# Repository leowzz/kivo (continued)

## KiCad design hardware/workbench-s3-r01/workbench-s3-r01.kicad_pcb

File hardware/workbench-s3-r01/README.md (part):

# Workbench S3 r01 - Stacked Breakaway Boards

Independent **routed prototype**, using the YD ESP32-S3 core board from
`refer/YD-ESP32-S3/`. Open `workbench-s3-r01.kicad_pro` in KiCad 10.
The RP2040 design remains in `../workbench-r03/`. Physical module fit and
the fabricator's panel process still require confirmation; this is not a
released product definition. Firmware support remains pending.

## Architecture

- Manufacture a single mechanically connected 126 x 187 mm panel, then cut
  the perforated tabs into an upper key board and a lower controller board.
- Assemble the 126 x 86 mm lower board horizontally and the 126 x 98 mm upper
  board rear-high at a nominal 30 degrees. The PCB projection fits in 86 mm
  depth, compared with 135 mm for the previous single-board draft.
- J8 on the lower board and J9 on the upper underside connect by one **four-wire
  harness: GND, 3V3, SDA, SCL**. No electrical connection crosses the tabs.
- Preassembled YD ESP32-S3 plugs into two 1x22 female sockets, J1 and J7.
- Reuse the core board's native USB Type-C for HID/data and power.
- 18 MX hot-swap keys use a 3x6 matrix with one 1N4148W diode per key.
- An upper-board MCP23017 scans the matrix and five control inputs; it shares
  the display's I2C bus. The application uses just **two ESP32 GPIOs**, 13/14.
- SH1106/EC11/confirm/back module connects by the J2 harness.
- J4 exposes 22 general-purpose spare GPIOs, GND and 3.3 V.
- J5/J6 provide external BOOT/RESET button connections.
- Carrier parts are through-hole connectors, SOD-123 diodes, 0805 passives
  with extended pads, and one SOIC-28 wide chip with 1.27 mm lead pitch.
- No bare MCU, flash, crystal, regulator or fine-pitch USB connector needs
  soldering on this carrier.

## Schematic Pages

Open `workbench-s3-r01.kicad_sch` as the root schematic. Page 1 (A4) contains
the lower board's core sockets, expansion header, BOOT/RESET and J8 cable
connector. Its `Upper` sheet opens page 2 (A3), containing the upper board's
power entry, MCP23017 with local decoupling/reset/I2C pull-ups, display
connector and directly wired 3x6 key/diode matrix. Both schematic files are
required when copying the project.

The upper sheet uses absolute global labels such as `/UP_GPA5` to preserve
the existing routed PCB net names. They do not connect to the lower board;
the external J8/J9 harness still joins the two independent circuits. The
layout retains all component values, footprints, reference designators and
symbol UUIDs. The PCB's upper-component schematic paths are updated for the
new hierarchy; copper, footprints and board geometry are unchanged.

`layout_workbench_s3_schematic.py` provides the shared page layout used by
the generator. `placement.json` records the two schematic paths so a fresh
placement keeps the correct symbol associations. A before/after exported
netlist can be checked using `verify_workbench_s3_schematic.py`.

## Core Board Sockets

The manufacturer's metric drawing specifies 27.94 mm width, 57.15 mm PCB
length, 63.39 mm including the antenna, 25.40 mm between header rows and
53.34 mm between the first and last holes. Both rows have 22 pins at 2.54 mm
pitch; end holes are approximately 1.91 mm from each PCB end.

Viewed from the carrier's component side with USB at the rear/top:

| Carrier | Core Board Row | Position | Pin 1 |
| --- | --- | --- | --- |
| J1 | Manufacturer P1 | Right | 3V3, nearest antenna/front |
| J7 | Manufacturer P2 | Left | GND, nearest antenna/front |

Both socket rows run from pin 1 towards pin 22 at the USB end. The core board
is rotated 180 degrees from the manufacturer's antenna-up illustration.
Use 2.54 mm female sockets with 1.0 mm PCB drills. The two row centers are
25.40 mm apart; do not substitute a narrower ESP32 board footprint.

The full pin mapping, including deliberately unconnected pins, is in
`placement.json`. GPIO19/20 stay exclusively on the module's USB connection.
GPIO35-37 are not used, allowing modules with octal PSRAM. GPIO43/44 remain
with the serial bridge, GPIO48 with the module RGB LED, and GPIO3/45/46 are
not assigned external loads because of boot-strapping constraints.

Power the assembly through the core board. The carrier uses its 3.3 V and GND.
P1 pin 21 is intentionally unconnected: the reference board's 5V pin is on
the input side of diode D3 unless its IN-OUT jumper is fitted. It must not
be assumed to provide USB-derived 5 V. External GPIO and I2C signals are
3.3 V only, and peripheral loads must fit the module regulator's remaining
current and thermal budget.

## Matrix

| Function | MCP23017 Ports |
| --- | --- |
| Rows R0-R2, selected LOW, inactive HIGH | GPA5, GPA6, GPA7 |
| Columns C0-C5, read with internal pull-ups | GPB0, GPB1, GPB2, GPB3, GPB4, GPB5 |

K1-K6 are the rear key row, K7-K12 the middle, and K13-K18 the front.
For every key: column -> switch -> diode anode A -> diode cathode K -> row.
**The stripe on each diode goes to the row net.** D1 belongs to K1, and so on.
Use 1N4148W in SOD-123, not the smaller SOD-323 version.

U1 is **MCP23017-E/SO**, at I2C address **0x20** (A0/A1/A2 tied to ground).
Its SOIC-28 wide package has accessible 1.27 mm pitch leads and no underside
thermal pad; assemble with a soldering iron, flux and solder wick. Do not
substitute MCP23S17 (SPI), SSOP or QFN for this footprint. R4 holds RESET
high, C3 is U1's local 100 nF decoupler, and C1/C2 decouple the upper supply.

The current Microchip datasheet specifies **GPA7 and GPB7 as output-only**.
GPA7 is a row output here; GPB7 is unused. GPB6 is also unused. GPA0-GPA4
read the display module's five control signals. INTA/INTB are unconnected;
firmware polls the ports so the harness needs no interrupt conductor.

This changes total application use from 16 MCU GPIOs to 2, and the inter-board
cable from 20 conductors to 4. Diodes prevent electrical ghost paths; firmware
must still implement matrix debounce and rollover behavior. Configure unused
ports to defined states and preload all row output latches HIGH before
enabling row outputs, then select one LOW at a time.

## Other Interfaces

All pin orders below use each separated board's front/component-side view,
rear edge at the top. The lower board is rotated 180 degrees in the panel.

| J2 Pin | Signal | Destination |
| --- | --- | --- |
| 1, rightmost square pad | VCC / 3.3 V | - |
| 2 | GND | - |
| 3 | BAK / KEY0 / Back | U1 GPA4 |
| 4 | TRB / TRIM_B / Encoder B | U1 GPA3 |
| 5 | TRA / TRIM_A / Encoder A | U1 GPA2 |
| 6 | PSH / PUSH / Encoder press | U1 GPA1 |
| 7 | SCL / IIC_SCL | ESP32 GPIO14 / U1 SCL |
| 8 | SDA / IIC_SDA | ESP32 GPIO13 / U1 SDA |
| 9, leftmost pad | CON / KEY1 / Confirm | U1 GPA0 |

J2 matches the supplied module interface diagram and front photograph in
`references/display-interface.png`. Looking at the readable display with
the encoder on the right, the top connector reads **CON, SDA, SCL, PSH,
TRA, TRB, BAK, GND, VCC from left to right**. This is pin 9 through pin 1.
VCC is **3.3 V only**. Use a pin-for-pin 9-wire harness and identify the
square pad rather than inferring pin numbers from a rear or mating-face view.
The module-side order is unchanged by this I2C revision; only the five
control signals' carrier-side destinations move from ESP32 GPIOs to U1.

The dimension source is `references/display-dimensions.png`. The module's
64.90 x 35.03 mm bounding rectangle is placed at upper-board `(8,3)` mm,
front-facing with the encoder on the right. `Dwgs.User` shows this assembly
envelope, including the notched board's full rectangular extent; it is not
a cutout in the carrier. The module connector runs horizontally near the
rear edge. Its leftmost pin is 11.38 mm from the module's left edge and
the row is 1.93 mm below its top edge. On the carrier, J2 pin 9 is at
`(19.38,4.93)` and pin 1 is at `(39.70,4.93)` mm.

The 2.54 mm header pitch is the standard pitch assumed for this module;
it is not explicitly dimensioned in the supplied drawing. Pin 1's X value
uses `11.38 + 8 * 2.54 = 31.70` mm. Confirm pitch against the purchased
module before fabrication. Carrier J2 uses 1.0 mm plated drills.

Four additional 3.4 mm NPTH clearance holes follow the module's M3 mounting
centers. The drawing's slight asymmetry is retained:

| Mount | Relative To Module Top-Left | Relative To Upper PCB Top-Left |
| --- | --- | --- |
| H_D1, rear left | (2.87, 2.85) | (10.87, 5.85) |
| H_D2, rear right | (61.90, 2.90) | (69.90, 5.90) |
| H_D3, front left | (2.95, 32.06) | (10.95, 35.06) |
| H_D4, front right | (61.93, 31.88) | (69.93, 34.88) |

These module mounts are separate from the upper PCB's four enclosure mounts.
Set module standoff height and header/harness direction from the actual
assembly; this connector is still a harness interface, not a validated
rigid board-to-board mating stack. Keep underside screw heads within the
3.5 mm nominal parts envelope or recheck the stack clearances.

R1/R2 are fitted **2.2 kohm I2C pull-ups to 3.3 V**. Include the display's
parallel pull-ups when calculating the effective resistance. For example,
2.2k in parallel with 4.7k is about 1.5k. Verify low-level sink current and
rise time with both harnesses attached; target at most 300 ns rise time at
400 kHz. Do not connect a module whose I2C pull-ups go to 5 V.

J4 sits at the lower board's rear-left edge. Its 1x24, 2.54 mm pitch plated holes have
1.0 mm drills. From the left square pad to the right:

| Pins | Signals In Pin Order |
| --- | --- |
| 1-6 | GND, 3V3, GPIO1, GPIO2, GPIO4, GPIO5 |
| 7-12 | GPIO6, GPIO7, GPIO8, GPIO9, GPIO10, GPIO11 |
| 13-18 | GPIO12, GPIO15, GPIO16, GPIO17, GPIO18, GPIO21 |
| 19-24 | GPIO38, GPIO39, GPIO40, GPIO41, GPIO42, GPIO47 |

Pin 1 is at `(10,3)` mm and pin 24 at `(68.42,3)` mm. The two button
headers move right to leave this longer expansion row clear: BOOT pin 1
at `(73,4)` and RESET pin 1 at `(80,4)` mm.

J5/J6 sit next to the core board's USB end. Each has two 2.54 mm pitch,
1.0 mm drilled plated holes for a normally-open momentary button with matching
leads, or short wires to a button. These are not universal four-leg button
footprints.

| Header | Left Square Pad, Pin 1 | Right Pad, Pin 2 |
| --- | --- | --- |
| J5 BOOT | GPIO0 | GND |
| J6 RESET | EN / CHIP_PU | GND |

They parallel the core board buttons. R3 adds a 10 kohm BOOT pull-up; the
module already supplies the EN pull-up and reset capacitors. Hold BOOT,
press/release RESET, then release BOOT to request the ROM download mode.

## Board-to-Board Cable

Use two **JST XH B4B-XH-A, 1x4, 2.50 mm pitch, vertical through-hole
headers** and matching XHP-4 housings/crimp contacts. Buy a precrimped,
pin-for-pin four-conductor harness to avoid soldering cable contacts.
Start with 150 mm including service slack. This is **2.50 mm XH**, not a
2.54 mm pin-header or IDC footprint; the PCB drills are 0.95 mm. Match the
actual header and housing dimensions before buying compatible parts.

J8 mounts on the lower board's top; J9 mounts on the upper board's bottom.
They face into the space between boards. The connection is **pin 1 to pin 1,
through pin 4 to pin 4**. Use the square PCB pad and the actual connector
pin numbering, not wire colors or a mirrored mating-face view. Prewired
cables can reverse the pin order: check continuity before powering the assembly.
J8 pin 1 is at lower `(47,25)` and J9 pin 1 at upper `(83,8)` mm.
Viewed through each board from the front, pin numbers increase towards +X;
the underside mating view is mirrored. The keyed housings face into the stack.

| Pins | Signals In Pin Order |
| --- | --- |
| 1-4 | GND, 3V3, SDA / GPIO13, SCL / GPIO14 |

`interconnect.csv` is the complete pin-by-pin mapping. Upper-board schematic
nets use `UP_` prefixes, including `UP_GND` and `UP_3V3`; lower-board nets use
the original names. The external cable joins these separate circuit domains.
Never merge the names or route across the breakaway tabs to remove airwires.
Start bring-up at 100 kHz, then validate 400 kHz with the actual harnesses.
The OLED and MCP23017 share this bus; confirm the OLED's 0x3C/0x3D address
and the expander's 0x20 address. Four conductors meet the minimum for this
shared I2C bus plus supply/ground. Further reduction would need a different
protocol or additional active circuitry and would complicate this assembly.

## Panel And Separation

Both boards use two copper layers and 1.6 mm FR-4. Panel coordinates below
start at the top-left of the outline; KiCad drawing coordinates add 50 mm
to X and Y.

| Section | Panel Coordinates | Finished Size |
| --- | --- | --- |
| Upper | X 0-126, Y 0-98 | 126 x 98 mm |
| Routed separation channel | Y 98-101 | 3 mm wide |
| Lower, rotated 180 degrees | X 0-126, Y 101-187 | 126 x 86 mm |

The lower-board transform is `(panel_x, panel_y) = (126-x, 187-y)`.
Rotate it back 180 degrees in-plane after separation. Its sockets remain
on the top side, with Type-C at the rear. Do not turn the lower board over.

Two internal racetrack slots and open side notches leave three nominal
5 mm wide tab necks centered at X 20, 63 and 106 mm. Each tab has two rows of
six **0.5 mm NPTH holes at 0.8 mm pitch**, at Y 98.75 and 100.25: 36 holes
total. `Edge.Cuts` defines the actual routed slots; the holes are drilling
features. This is tab routing with mouse bites, not a V-score line.

Cut both perforated rows with flush cutters while supporting each board,
then file the remaining tab stubs back to Y 98 and Y 101. The outer holes
leave roughly 1.25 mm of stub at each finished edge; the two rectangular
separated-board previews assume these stubs have been removed. Separate and
deburr the bare panel before soldering. Do not bend the panel with the
core board, display or other parts installed.

The Y 96-103 band forbids copper tracks, vias and pours on both layers.
Only mechanical holes are permitted there; the verifier also checks that
electrical pads stay out. Each finished board has its own four M3 enclosure
mounting holes, in addition to the upper board's four display mounts, so the
tabs carry no load in the finished assembly.

All 12 mounting holes have a 3.0 mm radius keepout on both copper layers,
covering the specified maximum 5.6 mm screw heads. Use matching small-head
M3 screws; larger heads or washers need a new clearance check.

Confirm the slot tooling, perforation drill/spacing, tab strength and
customer-panelization policy with the chosen fabricator before ordering.
Two circuits connected by tabs may still be charged as two designs; the
126 x 187 mm panel area is larger than the previous single board. A shorter
enclosure does not imply cheaper PCB fabrication or lower print volume.

## Stacked Assembly

Nominal dimensions are in `placement.json` under `stack`; the generated
`stack-side.png` and `stack-clearances.json` show an envelope study. They are
not a completed enclosure or a fitted model of the purchased parts.

- Lower PCB top is Z = 0; its rear edge is Y = 0, with USB facing outward.
- Upper PCB rear is also Y = 0. Tilt it 30 degrees, rear high/front low.
  Its front underside is Z = 25 mm and rear underside is Z = 74 mm.
- Including 1.6 mm board thickness, upper-board depth projects to 85.67 mm.
  The two boards therefore fit a nominal 126 x 86 mm PCB footprint.
- Allow a maximum core-board/socket envelope of Z = 20 mm, antenna top
  Z = 14.5 mm, upper underside parts of 3.5 mm, and mated XH envelopes
  of 12 mm. Under these assumptions, core-to-upper-parts clearance is
  14.69 mm normal to the upper plane; antenna clearance is 16.33 mm.
- The upper XH envelope clears the core envelope vertically by 38.18 mm.
  J8 is beside the core, not underneath it. Keep the cable loop left of the
  antenna and secure it away from key sockets and screw posts.
- Fix the upper board to sloped seats or angle brackets. Its four mounting
  holes do not align vertically with the lower holes; straight shared
  standoffs are not the intended mounting method.

The lower board's antenna aperture and two-layer keepout remain. Space to
the upper copper is included in the nominal study, but RF performance is
unmeasured. Keep metal, wiring and screws out of the antenna volume.

Measure the purchased core board, female socket height, plug engagement,
XH housings, button leads and display assembly before locking these heights.
The PCB footprint excludes keycaps, controls, enclosure walls, feet and USB
plug clearance. Provide a removable top for unplugging the core board and
support hot-swap sockets with the switch plate. Existing STL/CAD models have
not been regenerated; the new enclosure must follow this stacked assembly.

## Hand Assembly

1. Cut and deburr the bare panel, then clean both boards before fitting parts.
2. Solder U1 on the upper front first: align pin 1 with its marker, tack
   opposite corners, then solder the visible SOIC leads and inspect for
   bridges. Fit 0805 parts and 18 SOD-123 diodes; check every diode stripe.
3. Solder Kailh sockets on the back, keeping the iron and solder off plastic.
   Support each socket flat on the PCB; inspect both contacts for wetting.
4. Fit the two 1x22 female sockets using the unpowered core board as an
   alignment jig. Tack one end of each row, check seating, then finish.
5. Fit J8 on the lower top and J9 on the upper bottom, then the
   display/expansion headers and external buttons or wires.
6. Inspect bridges and polarity and measure supply-to-ground resistance
   before plugging in the core board or applying power. Verify all four cable
   connections pin-for-pin and confirm supply polarity at upper-board J2.

Buy one preassembled YD ESP32-S3 core board and two matching 1x22 male strips
if the core board is supplied without pins. `bom-draft.csv` lists the carrier
parts; the purchased core board, switch bodies, keycaps and display module
are separate assemblies. Ordinary soldering-iron assembly is intended.

## Routing

- Two copper layers, 0.25 mm signal tracks, 0.5 mm power branches and
  0.4 mm local power connections/socket escape. Minimum clearance is 0.2 mm.
- Through vias are 0.6 mm diameter with 0.3 mm drills, tented on both sides.
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
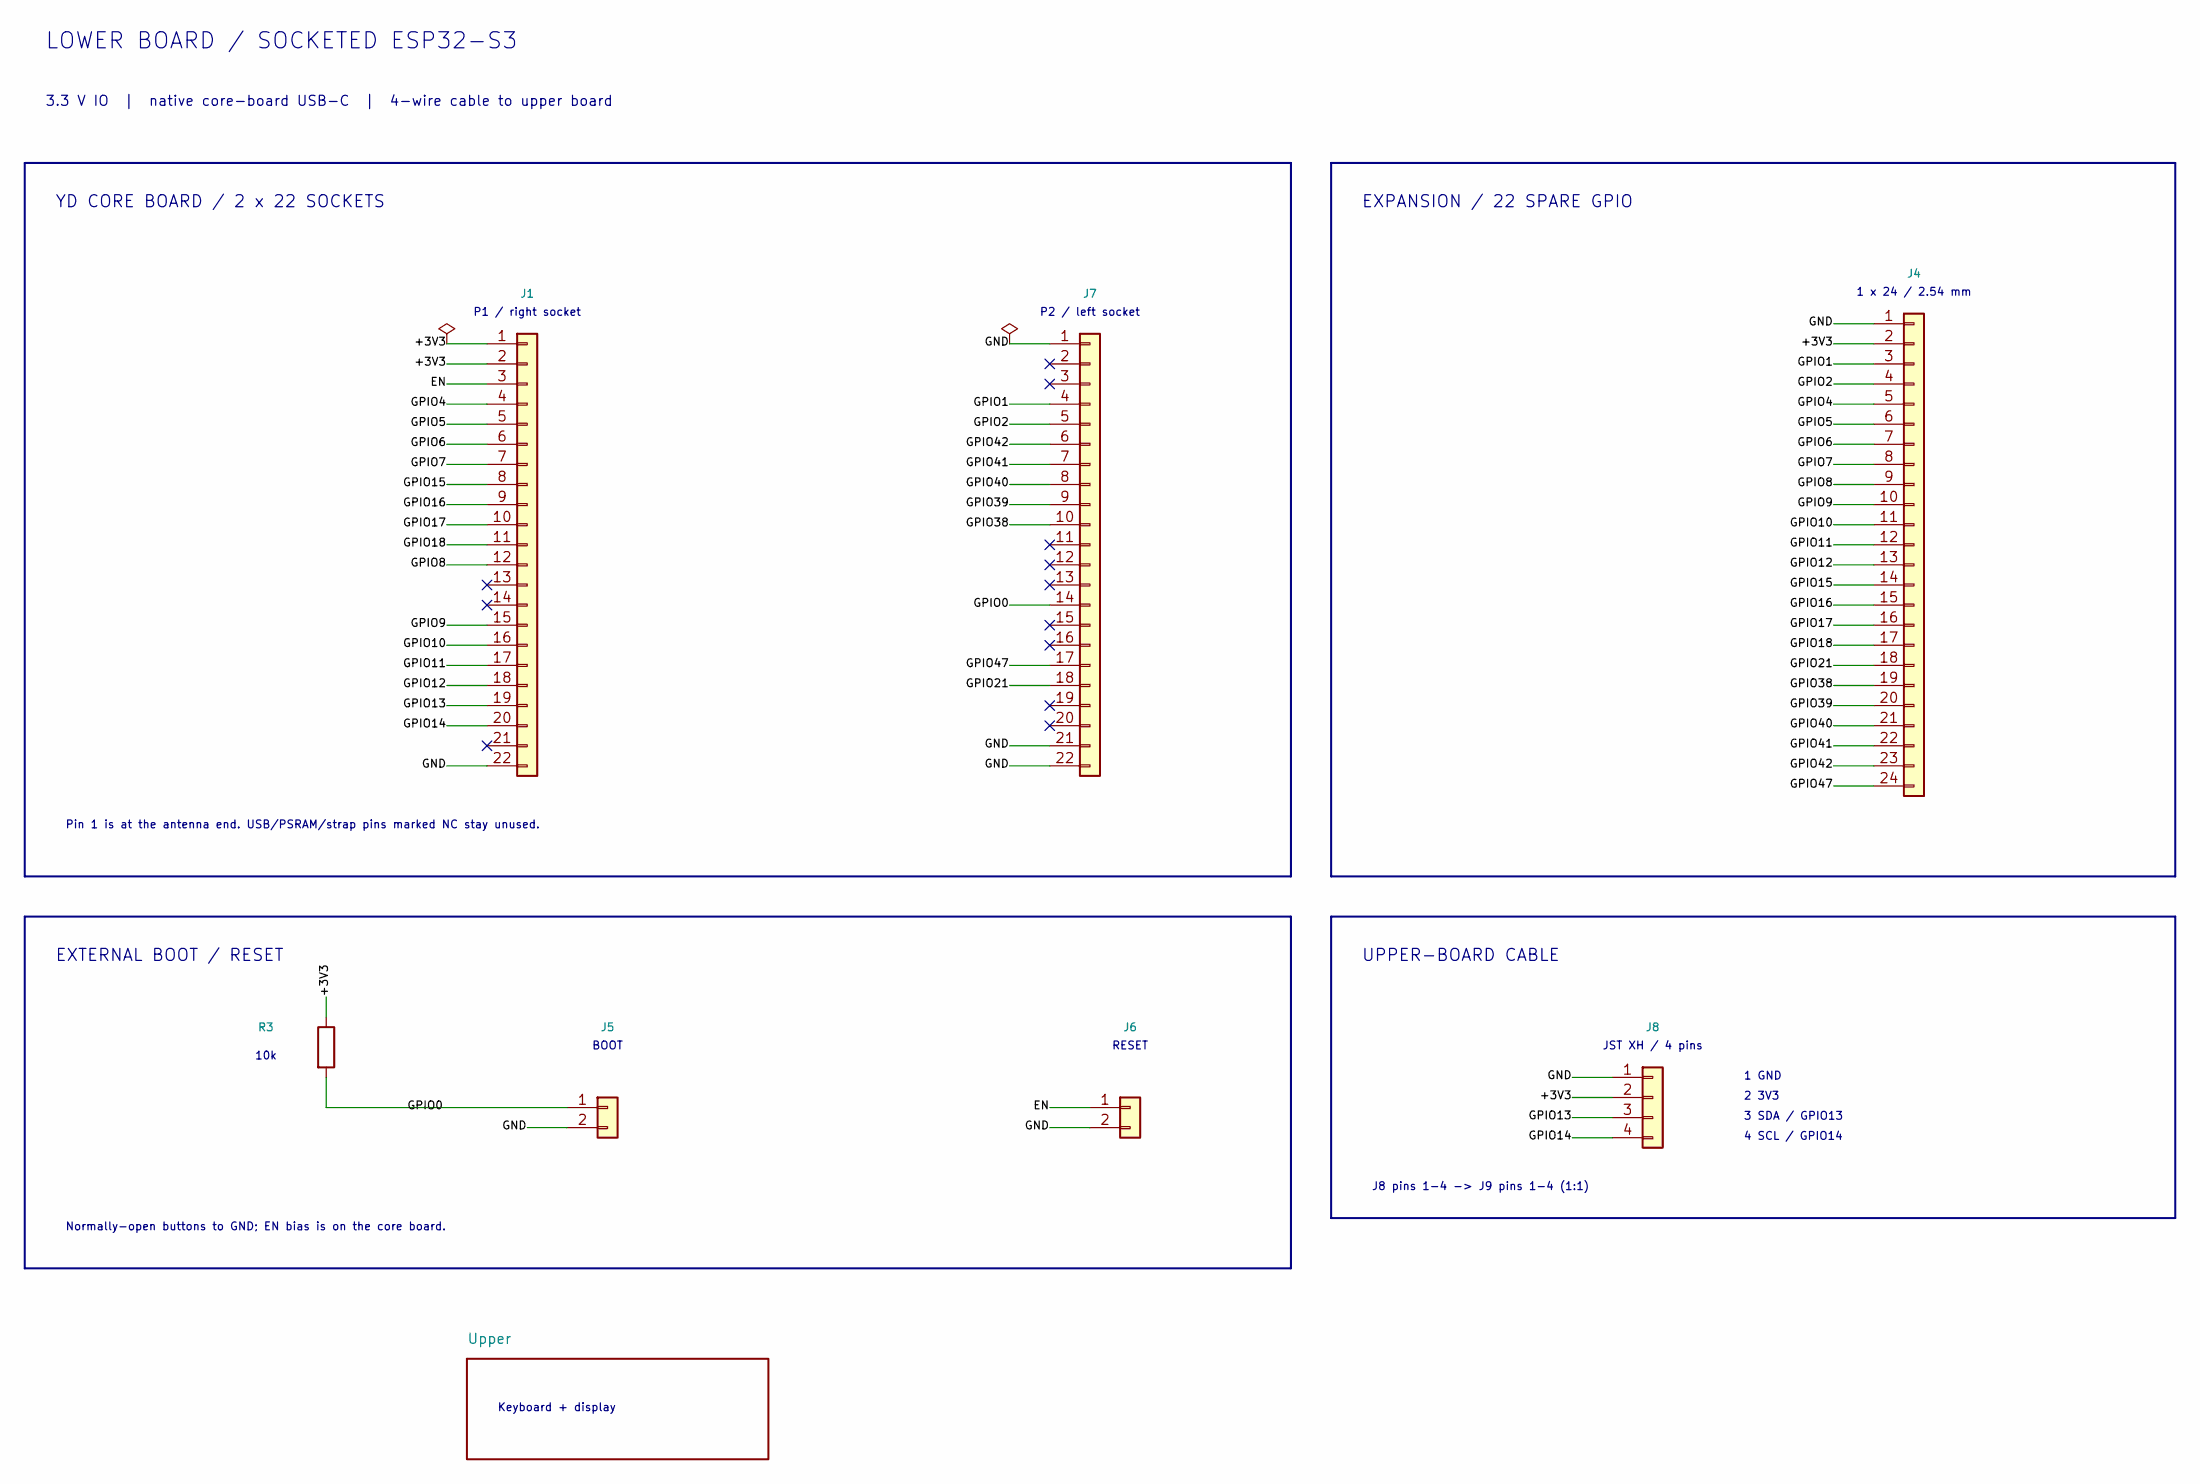
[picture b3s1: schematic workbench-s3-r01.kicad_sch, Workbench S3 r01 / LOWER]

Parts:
J1: YD P1 / RIGHT SOCKET / 1x22; PinSocket_1x22_P2.54mm_Vertical
J4: EXPANSION / 22 SPARE GPIO / 3V3 IO; PinHeader_1x24_P2.54mm_Vertical
J5: EXTERNAL BOOT / GPIO0 TO GND; PinHeader_1x02_P2.54mm_Vertical
J6: EXTERNAL RESET / EN TO GND; PinHeader_1x02_P2.54mm_Vertical
J7: YD P2 / LEFT SOCKET / 1x22; PinSocket_1x22_P2.54mm_Vertical
J8: LOWER / I2C4 TO J9 / 1:1; JST_XH_B4B-XH-A_1x04_P2.50mm_Vertical
R3: 10k; R_0805_2012Metric_Pad1.20x1.40mm_HandSolder

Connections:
/+3V3: J1.1, J1.2, J4.2, J8.2, R3.1
/EN: J1.3, J6.1
/GND: J1.22, J4.1, J5.2, J6.2, J7.1, J7.21, J7.22, J8.1
/GPIO0: J5.1, J7.14, R3.2
/GPIO1: J4.3, J7.4
/GPIO2: J4.4, J7.5
/GPIO4: J1.4, J4.5
/GPIO5: J1.5, J4.6
/GPIO6: J1.6, J4.7
/GPIO7: J1.7, J4.8
/GPIO8: J1.12, J4.9
/GPIO9: J1.15, J4.10
/GPIO10: J1.16, J4.11
/GPIO11: J1.17, J4.12
/GPIO12: J1.18, J4.13
/GPIO13: J1.19, J8.3
/GPIO14: J1.20, J8.4
/GPIO15: J1.8, J4.14
/GPIO16: J1.9, J4.15
/GPIO17: J1.10, J4.16
/GPIO18: J1.11, J4.17
/GPIO21: J4.18, J7.18
/GPIO38: J4.19, J7.10
/GPIO39: J4.20, J7.9
/GPIO40: J4.21, J7.8
/GPIO41: J4.22, J7.7
/GPIO42: J4.23, J7.6
/GPIO47: J4.24, J7.17

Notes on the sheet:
LOWER BOARD / SOCKETED ESP32-S3
3.3 V IO | native core-board USB-C | 4-wire cable to upper board
YD CORE BOARD / 2 x 22 SOCKETS
EXPANSION / 22 SPARE GPIO
P1 / right socket
P2 / left socket
1 x 24 / 2.54 mm
Pin 1 is at the antenna end. USB/PSRAM/strap pins marked NC stay unused.
EXTERNAL BOOT / RESET
UPPER-BOARD CABLE
BOOT
RESET
10k
JST XH / 4 pins
1 GND
2 3V3
3 SDA / GPIO13
4 SCL / GPIO14
Normally-open buttons to GND; EN bias is on the core board.
J8 pins 1-4 -> J9 pins 1-4 (1:1)
Keyboard + display

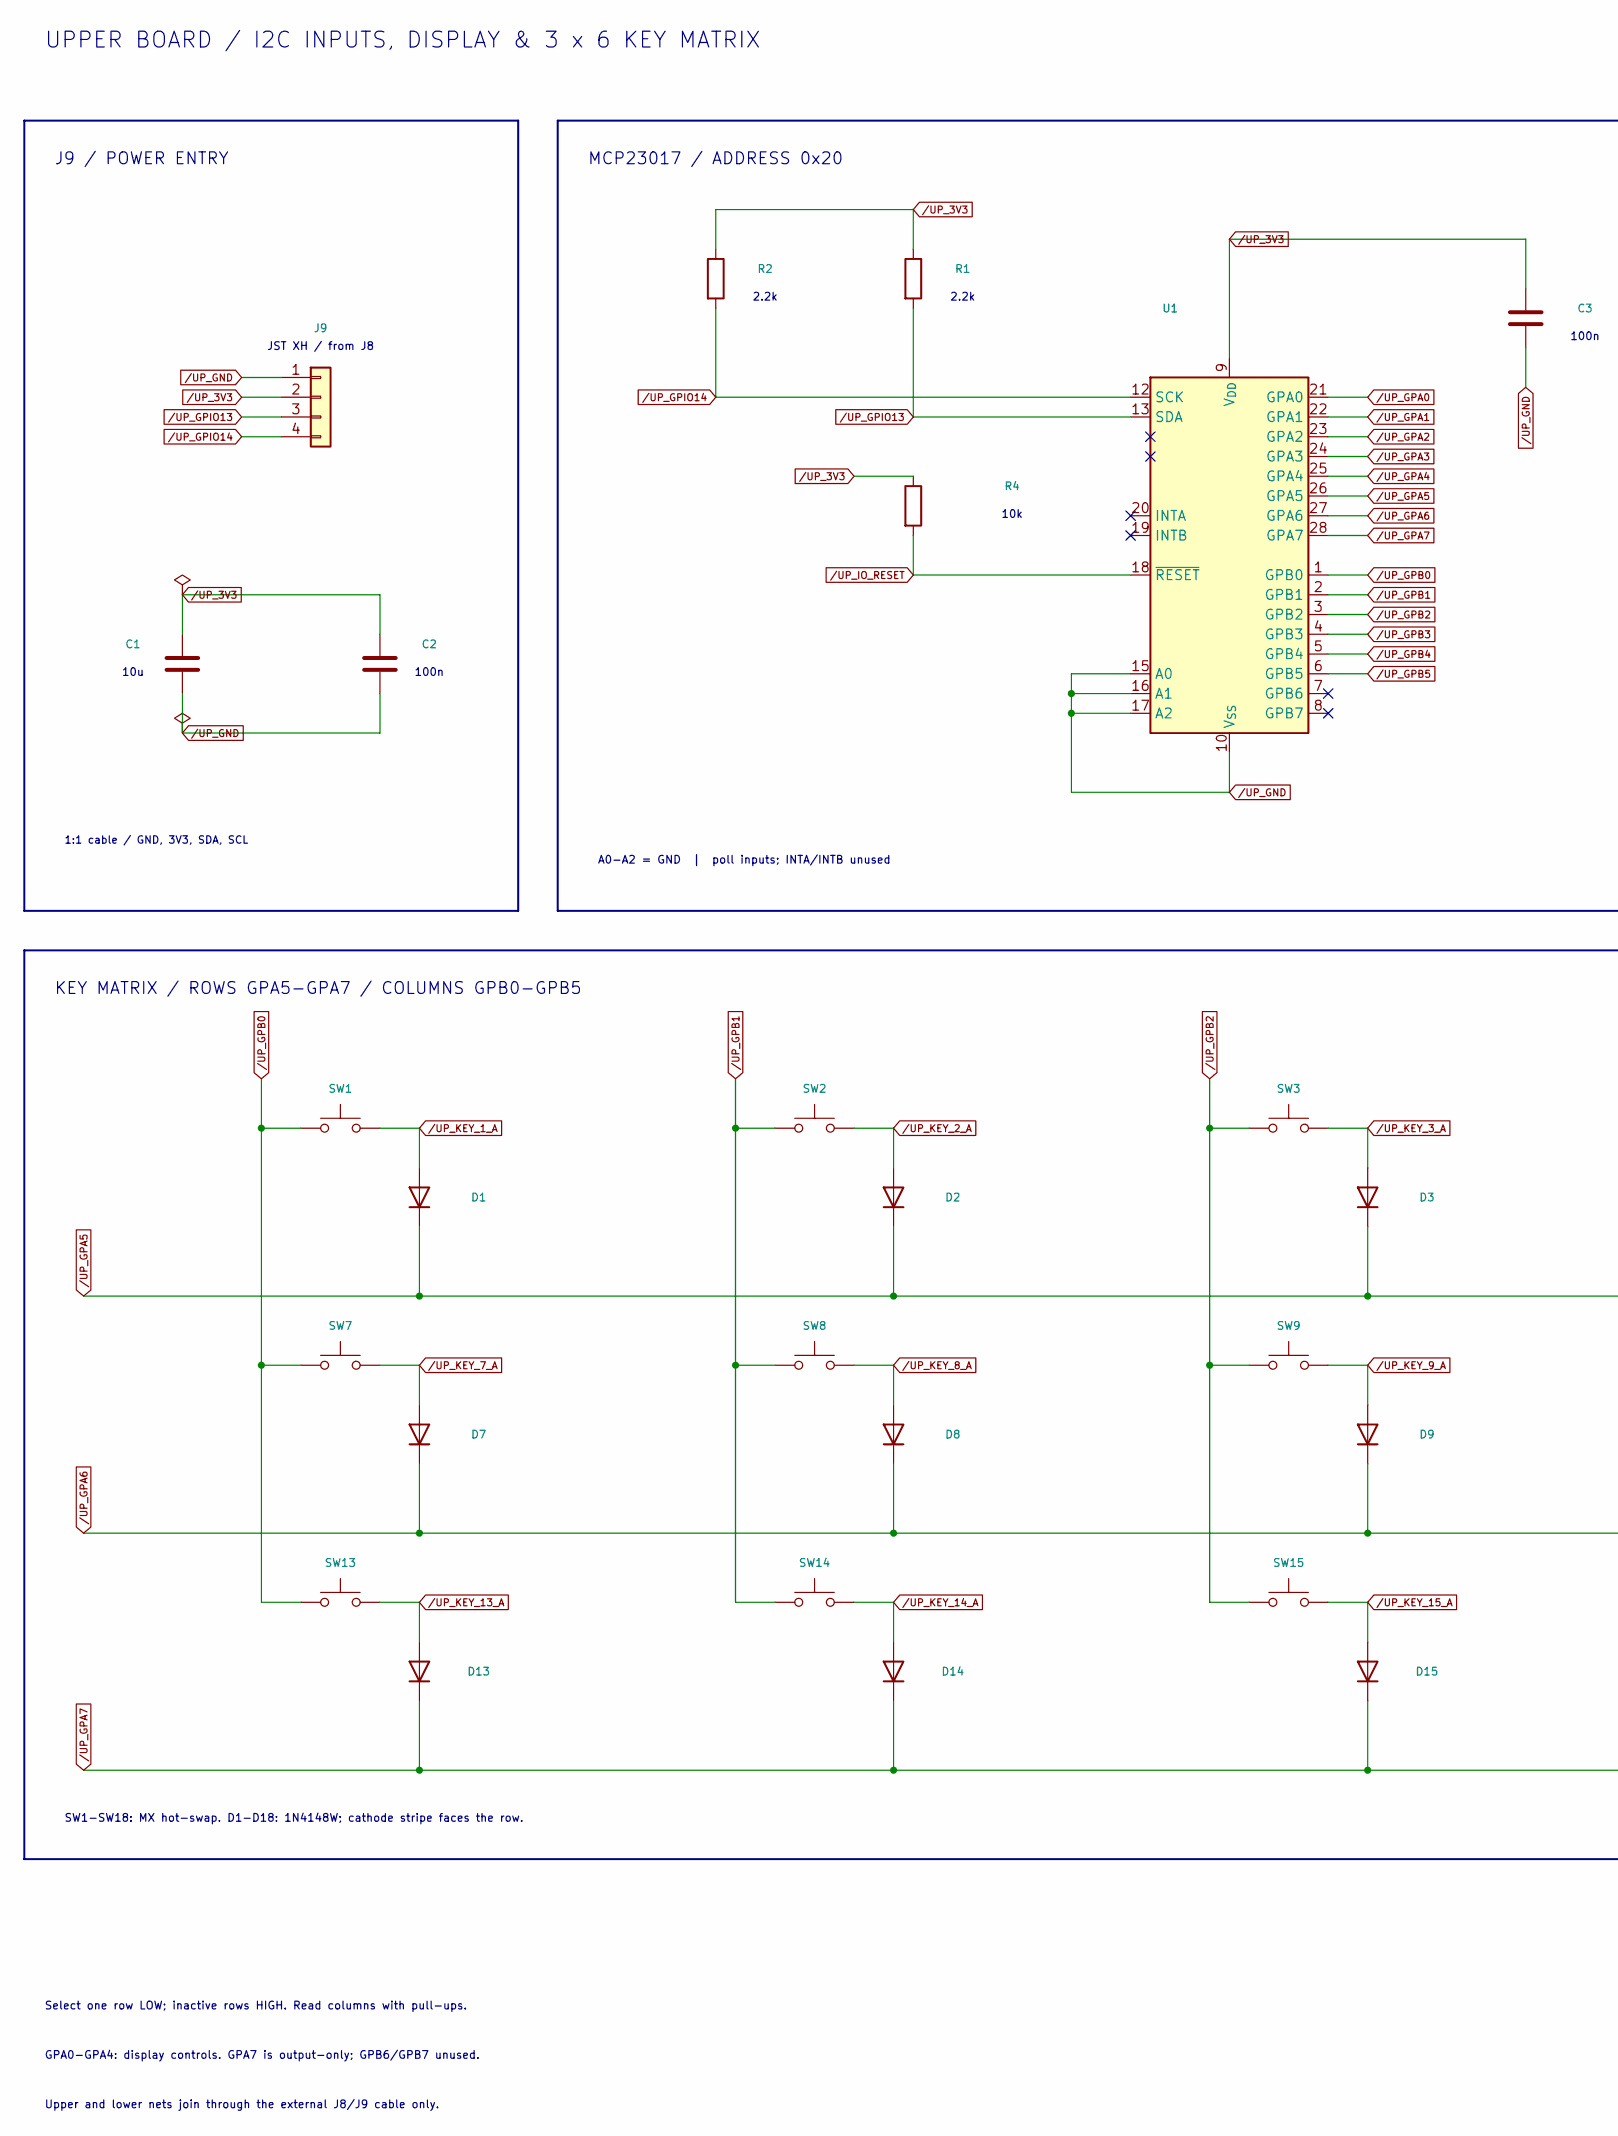
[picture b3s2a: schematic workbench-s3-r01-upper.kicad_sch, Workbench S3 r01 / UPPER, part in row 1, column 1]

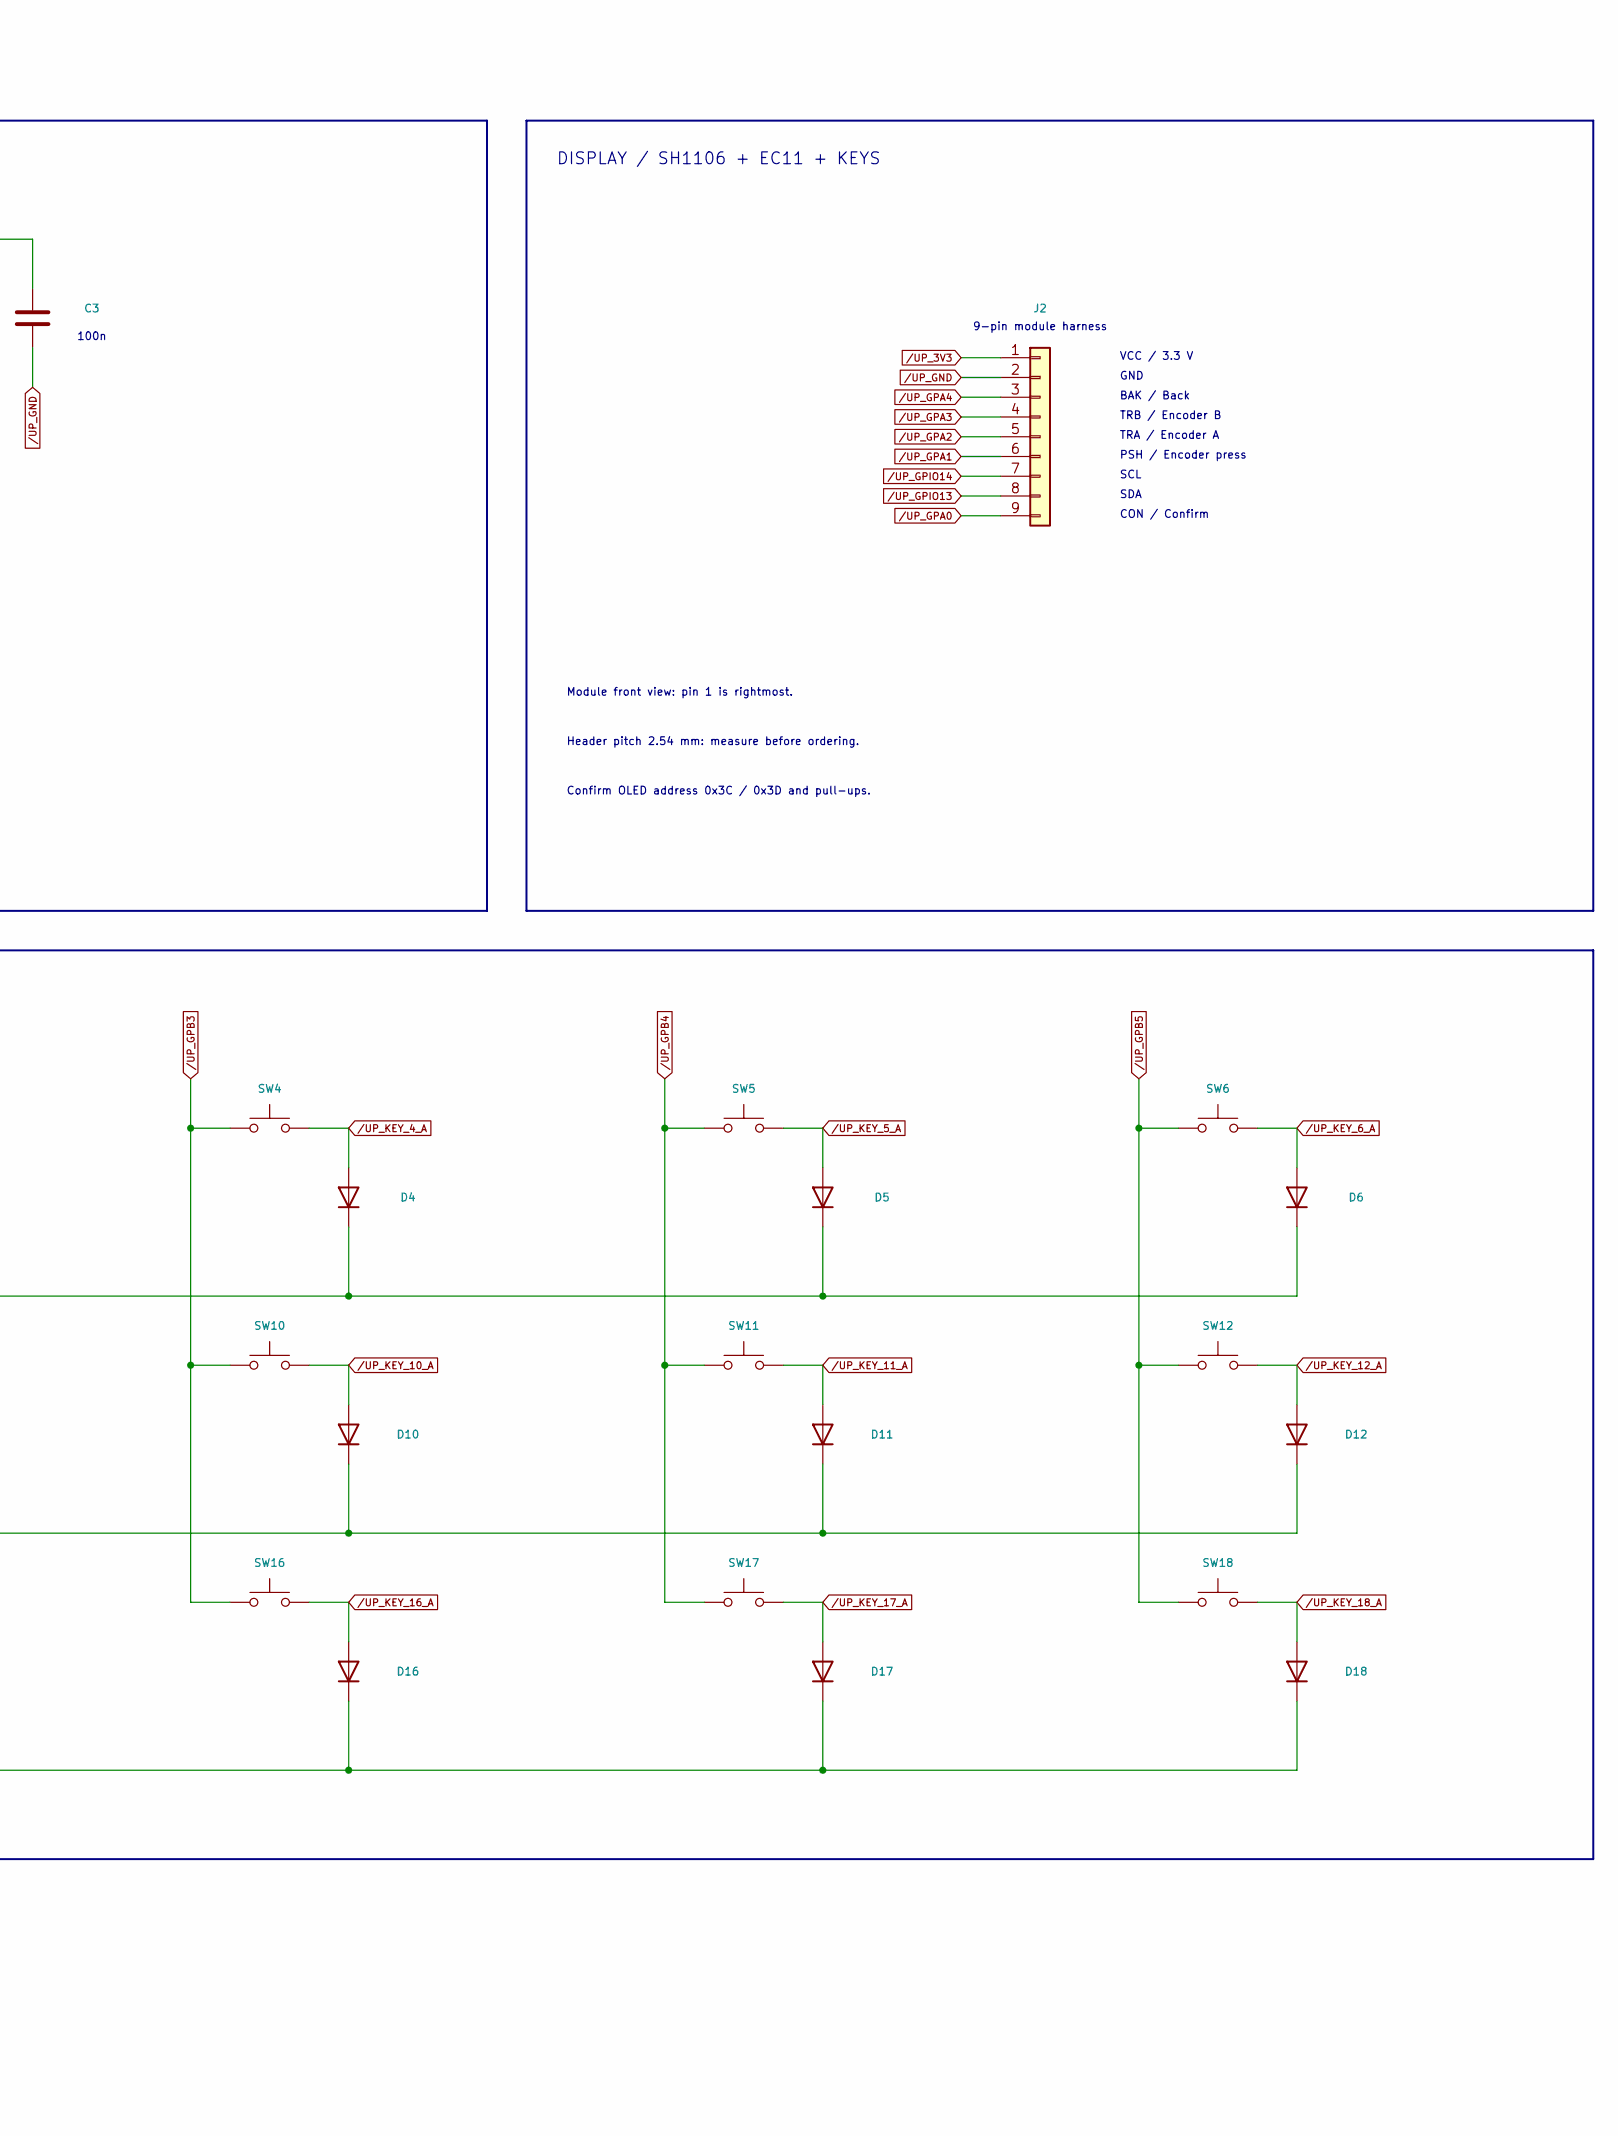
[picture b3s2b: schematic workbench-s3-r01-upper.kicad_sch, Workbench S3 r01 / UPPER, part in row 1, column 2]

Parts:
C1: 10u 10V X7R; C_0805_2012Metric_Pad1.18x1.45mm_HandSolder
C2: 100n 16V X7R; C_0805_2012Metric_Pad1.18x1.45mm_HandSolder
C3: 100n 16V X7R / U1; C_0805_2012Metric_Pad1.18x1.45mm_HandSolder
D1, D2, D3, D4, D5, D6, D7, D8, D9, D10, D11, D12, D13, D14, D15, D16, D17, D18: 1N4148W / K TO ROW; D_SOD-123
J2: DISPLAY / MODULE PIN 1 = 3V3; PinHeader_1x09_P2.54mm_Vertical
J9: UPPER / I2C4 TO J8 / 1:1; JST_XH_B4B-XH-A_1x04_P2.50mm_Vertical
R1, R2: 2.2k I2C PULLUP; R_0805_2012Metric_Pad1.20x1.40mm_HandSolder
R4: 10k U1 RESET PULLUP; R_0805_2012Metric_Pad1.20x1.40mm_HandSolder
SW1: KEY_1 MX HOTSWAP; keyswitch_cherrymx_hotswap_1u
SW2: KEY_2 MX HOTSWAP; keyswitch_cherrymx_hotswap_1u
SW3: KEY_3 MX HOTSWAP; keyswitch_cherrymx_hotswap_1u
SW4: KEY_4 MX HOTSWAP; keyswitch_cherrymx_hotswap_1u
SW5: KEY_5 MX HOTSWAP; keyswitch_cherrymx_hotswap_1u
SW6: KEY_6 MX HOTSWAP; keyswitch_cherrymx_hotswap_1u
SW7: KEY_7 MX HOTSWAP; keyswitch_cherrymx_hotswap_1u
SW8: KEY_8 MX HOTSWAP; keyswitch_cherrymx_hotswap_1u
SW9: KEY_9 MX HOTSWAP; keyswitch_cherrymx_hotswap_1u
SW10: KEY_10 MX HOTSWAP; keyswitch_cherrymx_hotswap_1u
SW11: KEY_11 MX HOTSWAP; keyswitch_cherrymx_hotswap_1u
SW12: KEY_12 MX HOTSWAP; keyswitch_cherrymx_hotswap_1u
SW13: KEY_13 MX HOTSWAP; keyswitch_cherrymx_hotswap_1u
SW14: KEY_14 MX HOTSWAP; keyswitch_cherrymx_hotswap_1u
SW15: KEY_15 MX HOTSWAP; keyswitch_cherrymx_hotswap_1u
SW16: KEY_16 MX HOTSWAP; keyswitch_cherrymx_hotswap_1u
SW17: KEY_17 MX HOTSWAP; keyswitch_cherrymx_hotswap_1u
SW18: KEY_18 MX HOTSWAP; keyswitch_cherrymx_hotswap_1u
U1: MCP23017-E/SO / 0x20; SOIC-28W_7.5x17.9mm_P1.27mm

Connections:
/UP_3V3: C1.1, C2.1, C3.1, J2.1, J9.2, R1.1, R2.1, R4.1, U1.9 (V_{DD})
/UP_GND: C1.2, C2.2, C3.2, J2.2, J9.1, U1.10 (V_{SS}), U1.15 (A0), U1.16 (A1), U1.17 (A2)
/UP_GPA0: J2.9, U1.21 (GPA0)
/UP_GPA1: J2.6, U1.22 (GPA1)
/UP_GPA2: J2.5, U1.23 (GPA2)
/UP_GPA3: J2.4, U1.24 (GPA3)
/UP_GPA4: J2.3, U1.25 (GPA4)
/UP_GPA5: D1.1 (K), D2.1 (K), D3.1 (K), D4.1 (K), D5.1 (K), D6.1 (K), U1.26 (GPA5)
/UP_GPA6: D7.1 (K), D8.1 (K), D9.1 (K), D10.1 (K), D11.1 (K), D12.1 (K), U1.27 (GPA6)
/UP_GPA7: D13.1 (K), D14.1 (K), D15.1 (K), D16.1 (K), D17.1 (K), D18.1 (K), U1.28 (GPA7)
/UP_GPB0: SW1.1, SW7.1, SW13.1, U1.1 (GPB0)
/UP_GPB1: SW2.1, SW8.1, SW14.1, U1.2 (GPB1)
/UP_GPB2: SW3.1, SW9.1, SW15.1, U1.3 (GPB2)
/UP_GPB3: SW4.1, SW10.1, SW16.1, U1.4 (GPB3)
/UP_GPB4: SW5.1, SW11.1, SW17.1, U1.5 (GPB4)
/UP_GPB5: SW6.1, SW12.1, SW18.1, U1.6 (GPB5)
/UP_GPIO13: J2.8, J9.3, R1.2, U1.13 (SDA)
/UP_GPIO14: J2.7, J9.4, R2.2, U1.12 (SCK)
/UP_IO_RESET: R4.2, U1.18 (~RESET)
/UP_KEY_1_A: D1.2 (A), SW1.2
/UP_KEY_2_A: D2.2 (A), SW2.2
/UP_KEY_3_A: D3.2 (A), SW3.2
/UP_KEY_4_A: D4.2 (A), SW4.2
/UP_KEY_5_A: D5.2 (A), SW5.2
/UP_KEY_6_A: D6.2 (A), SW6.2
/UP_KEY_7_A: D7.2 (A), SW7.2
/UP_KEY_8_A: D8.2 (A), SW8.2
/UP_KEY_9_A: D9.2 (A), SW9.2
/UP_KEY_10_A: D10.2 (A), SW10.2
/UP_KEY_11_A: D11.2 (A), SW11.2
/UP_KEY_12_A: D12.2 (A), SW12.2
/UP_KEY_13_A: D13.2 (A), SW13.2
/UP_KEY_14_A: D14.2 (A), SW14.2
/UP_KEY_15_A: D15.2 (A), SW15.2
/UP_KEY_16_A: D16.2 (A), SW16.2
/UP_KEY_17_A: D17.2 (A), SW17.2
/UP_KEY_18_A: D18.2 (A), SW18.2

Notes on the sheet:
UPPER BOARD / I2C INPUTS, DISPLAY & 3 x 6 KEY MATRIX
J9 / POWER ENTRY
MCP23017 / ADDRESS 0x20
DISPLAY / SH1106 + EC11 + KEYS
JST XH / from J8
10u
100n
1:1 cable / GND, 3V3, SDA, SCL
2.2k
10k
A0-A2 = GND | poll inputs; INTA/INTB unused
9-pin module harness
VCC / 3.3 V
GND
BAK / Back
TRB / Encoder B
TRA / Encoder A
PSH / Encoder press
SCL
SDA
CON / Confirm
Module front view: pin 1 is rightmost.
Header pitch 2.54 mm: measure before ordering.
Confirm OLED address 0x3C / 0x3D and pull-ups.
KEY MATRIX / ROWS GPA5-GPA7 / COLUMNS GPB0-GPB5
SW1-SW18: MX hot-swap. D1-D18: 1N4148W; cathode stripe faces the row.
Select one row LOW; inactive rows HIGH. Read columns with pull-ups.
GPA0-GPA4: display controls. GPA7 is output-only; GPB6/GPB7 unused.
Upper and lower nets join through the external J8/J9 cable only.

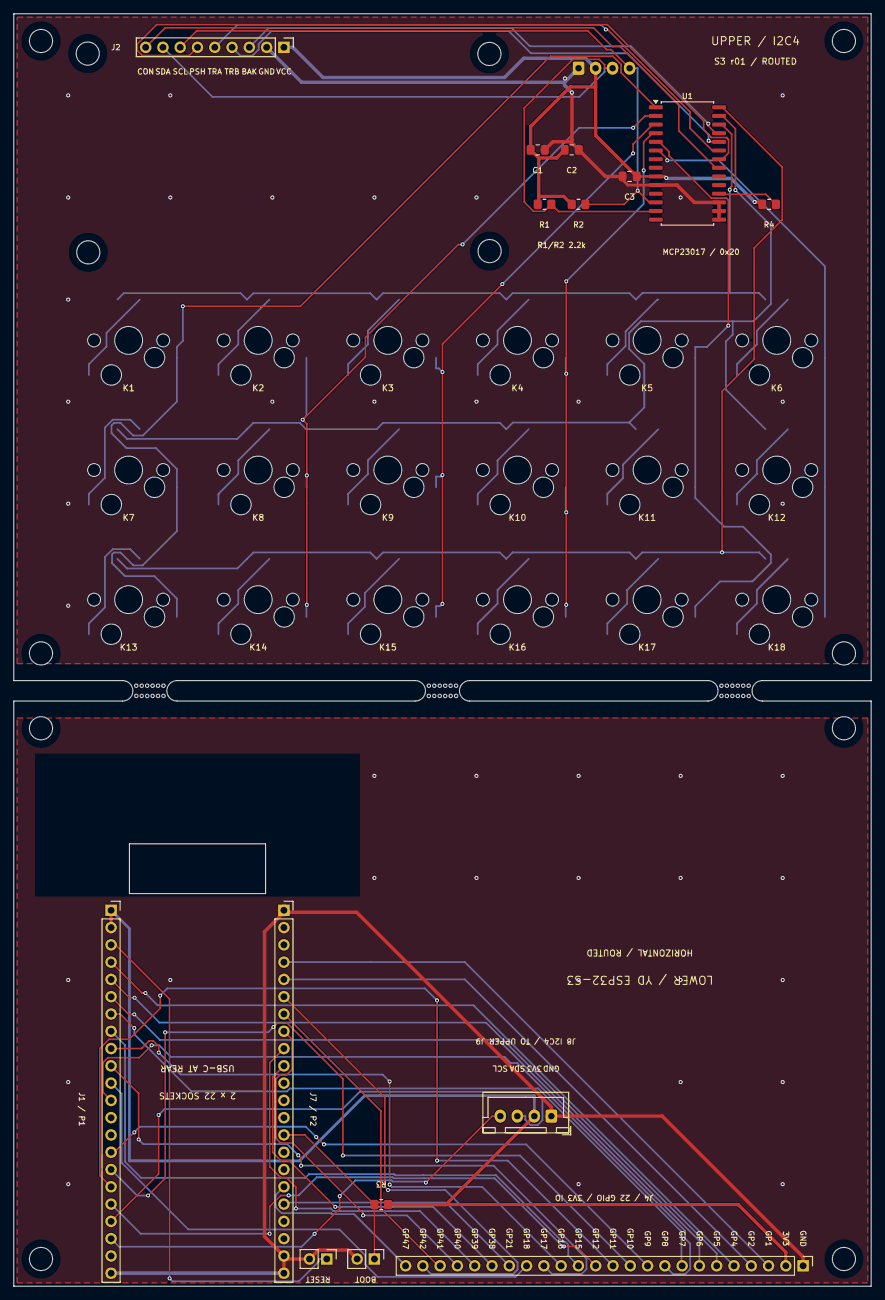
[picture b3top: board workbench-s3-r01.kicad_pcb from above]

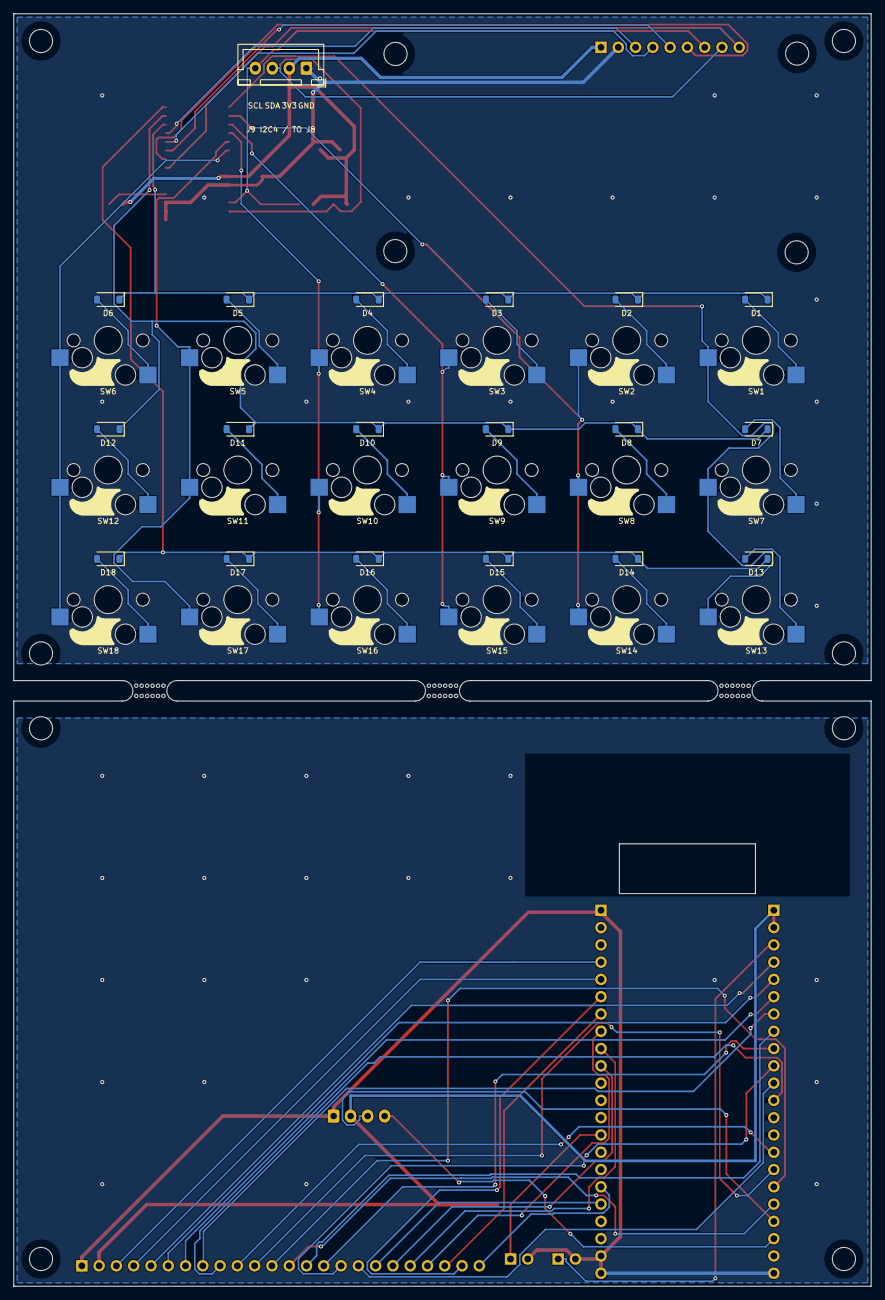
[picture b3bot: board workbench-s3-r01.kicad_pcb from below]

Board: 2 copper layers, 126.0 x 187.0 mm, 70 parts (37 on the bottom side), 65 nets.

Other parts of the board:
H_D1, H_D2, H_D3, H_D4: M3 head <=5.6mm; MountingHole_M3_5.6mm_Head
H_L1, H_L2, H_L3, H_L4: M3 head <=5.6mm; MountingHole_M3_5.6mm_Head
H_U1, H_U2, H_U3, H_U4: M3 head <=5.6mm; MountingHole_M3_5.6mm_Head
MB1, MB2, MB3, MB4, MB5, MB6: MouseBites_6x0.5_P0.8

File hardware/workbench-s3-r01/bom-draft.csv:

Reference,Value,Footprint,MPN,DNP
J1,YD P1 / RIGHT SOCKET / 1x22,Connector_PinSocket_2.54mm:PinSocket_1x22_P2.54mm_Vertical,,False
J7,YD P2 / LEFT SOCKET / 1x22,Connector_PinSocket_2.54mm:PinSocket_1x22_P2.54mm_Vertical,,False
J2,DISPLAY / MODULE PIN 1 = 3V3,Connector_PinHeader_2.54mm:PinHeader_1x09_P2.54mm_Vertical,,False
J4,EXPANSION / 22 SPARE GPIO / 3V3 IO,Connector_PinHeader_2.54mm:PinHeader_1x24_P2.54mm_Vertical,,False
J5,EXTERNAL BOOT / GPIO0 TO GND,Connector_PinHeader_2.54mm:PinHeader_1x02_P2.54mm_Vertical,,False
J6,EXTERNAL RESET / EN TO GND,Connector_PinHeader_2.54mm:PinHeader_1x02_P2.54mm_Vertical,,False
C1,10u 10V X7R,Capacitor_SMD:C_0805_2012Metric_Pad1.18x1.45mm_HandSolder,,False
C2,100n 16V X7R,Capacitor_SMD:C_0805_2012Metric_Pad1.18x1.45mm_HandSolder,,False
C3,100n 16V X7R / U1,Capacitor_SMD:C_0805_2012Metric_Pad1.18x1.45mm_HandSolder,,False
R1,2.2k I2C PULLUP,Resistor_SMD:R_0805_2012Metric_Pad1.20x1.40mm_HandSolder,,False
R2,2.2k I2C PULLUP,Resistor_SMD:R_0805_2012Metric_Pad1.20x1.40mm_HandSolder,,False
R3,10k,Resistor_SMD:R_0805_2012Metric_Pad1.20x1.40mm_HandSolder,,False
R4,10k U1 RESET PULLUP,Resistor_SMD:R_0805_2012Metric_Pad1.20x1.40mm_HandSolder,,False
U1,MCP23017-E/SO / 0x20,Package_SO:SOIC-28W_7.5x17.9mm_P1.27mm,MCP23017-E/SO,False
J8,LOWER / I2C4 TO J9 / 1:1,Connector_JST:JST_XH_B4B-XH-A_1x04_P2.50mm_Vertical,,False
J9,UPPER / I2C4 TO J8 / 1:1,Connector_JST:JST_XH_B4B-XH-A_1x04_P2.50mm_Vertical,,False
SW1,KEY_1 MX HOTSWAP,Workbench:keyswitch_cherrymx_hotswap_1u,,False
D1,1N4148W / K TO ROW,Diode_SMD:D_SOD-123,1N4148W,False
SW2,KEY_2 MX HOTSWAP,Workbench:keyswitch_cherrymx_hotswap_1u,,False
D2,1N4148W / K TO ROW,Diode_SMD:D_SOD-123,1N4148W,False
SW3,KEY_3 MX HOTSWAP,Workbench:keyswitch_cherrymx_hotswap_1u,,False
D3,1N4148W / K TO ROW,Diode_SMD:D_SOD-123,1N4148W,False
SW4,KEY_4 MX HOTSWAP,Workbench:keyswitch_cherrymx_hotswap_1u,,False
D4,1N4148W / K TO ROW,Diode_SMD:D_SOD-123,1N4148W,False
SW5,KEY_5 MX HOTSWAP,Workbench:keyswitch_cherrymx_hotswap_1u,,False
D5,1N4148W / K TO ROW,Diode_SMD:D_SOD-123,1N4148W,False
SW6,KEY_6 MX HOTSWAP,Workbench:keyswitch_cherrymx_hotswap_1u,,False
D6,1N4148W / K TO ROW,Diode_SMD:D_SOD-123,1N4148W,False
SW7,KEY_7 MX HOTSWAP,Workbench:keyswitch_cherrymx_hotswap_1u,,False
D7,1N4148W / K TO ROW,Diode_SMD:D_SOD-123,1N4148W,False
SW8,KEY_8 MX HOTSWAP,Workbench:keyswitch_cherrymx_hotswap_1u,,False
D8,1N4148W / K TO ROW,Diode_SMD:D_SOD-123,1N4148W,False
SW9,KEY_9 MX HOTSWAP,Workbench:keyswitch_cherrymx_hotswap_1u,,False
D9,1N4148W / K TO ROW,Diode_SMD:D_SOD-123,1N4148W,False
SW10,KEY_10 MX HOTSWAP,Workbench:keyswitch_cherrymx_hotswap_1u,,False
D10,1N4148W / K TO ROW,Diode_SMD:D_SOD-123,1N4148W,False
SW11,KEY_11 MX HOTSWAP,Workbench:keyswitch_cherrymx_hotswap_1u,,False
D11,1N4148W / K TO ROW,Diode_SMD:D_SOD-123,1N4148W,False
SW12,KEY_12 MX HOTSWAP,Workbench:keyswitch_cherrymx_hotswap_1u,,False
D12,1N4148W / K TO ROW,Diode_SMD:D_SOD-123,1N4148W,False
SW13,KEY_13 MX HOTSWAP,Workbench:keyswitch_cherrymx_hotswap_1u,,False
D13,1N4148W / K TO ROW,Diode_SMD:D_SOD-123,1N4148W,False
SW14,KEY_14 MX HOTSWAP,Workbench:keyswitch_cherrymx_hotswap_1u,,False
D14,1N4148W / K TO ROW,Diode_SMD:D_SOD-123,1N4148W,False
SW15,KEY_15 MX HOTSWAP,Workbench:keyswitch_cherrymx_hotswap_1u,,False
D15,1N4148W / K TO ROW,Diode_SMD:D_SOD-123,1N4148W,False
SW16,KEY_16 MX HOTSWAP,Workbench:keyswitch_cherrymx_hotswap_1u,,False
D16,1N4148W / K TO ROW,Diode_SMD:D_SOD-123,1N4148W,False
SW17,KEY_17 MX HOTSWAP,Workbench:keyswitch_cherrymx_hotswap_1u,,False
D17,1N4148W / K TO ROW,Diode_SMD:D_SOD-123,1N4148W,False
SW18,KEY_18 MX HOTSWAP,Workbench:keyswitch_cherrymx_hotswap_1u,,False
D18,1N4148W / K TO ROW,Diode_SMD:D_SOD-123,1N4148W,False
